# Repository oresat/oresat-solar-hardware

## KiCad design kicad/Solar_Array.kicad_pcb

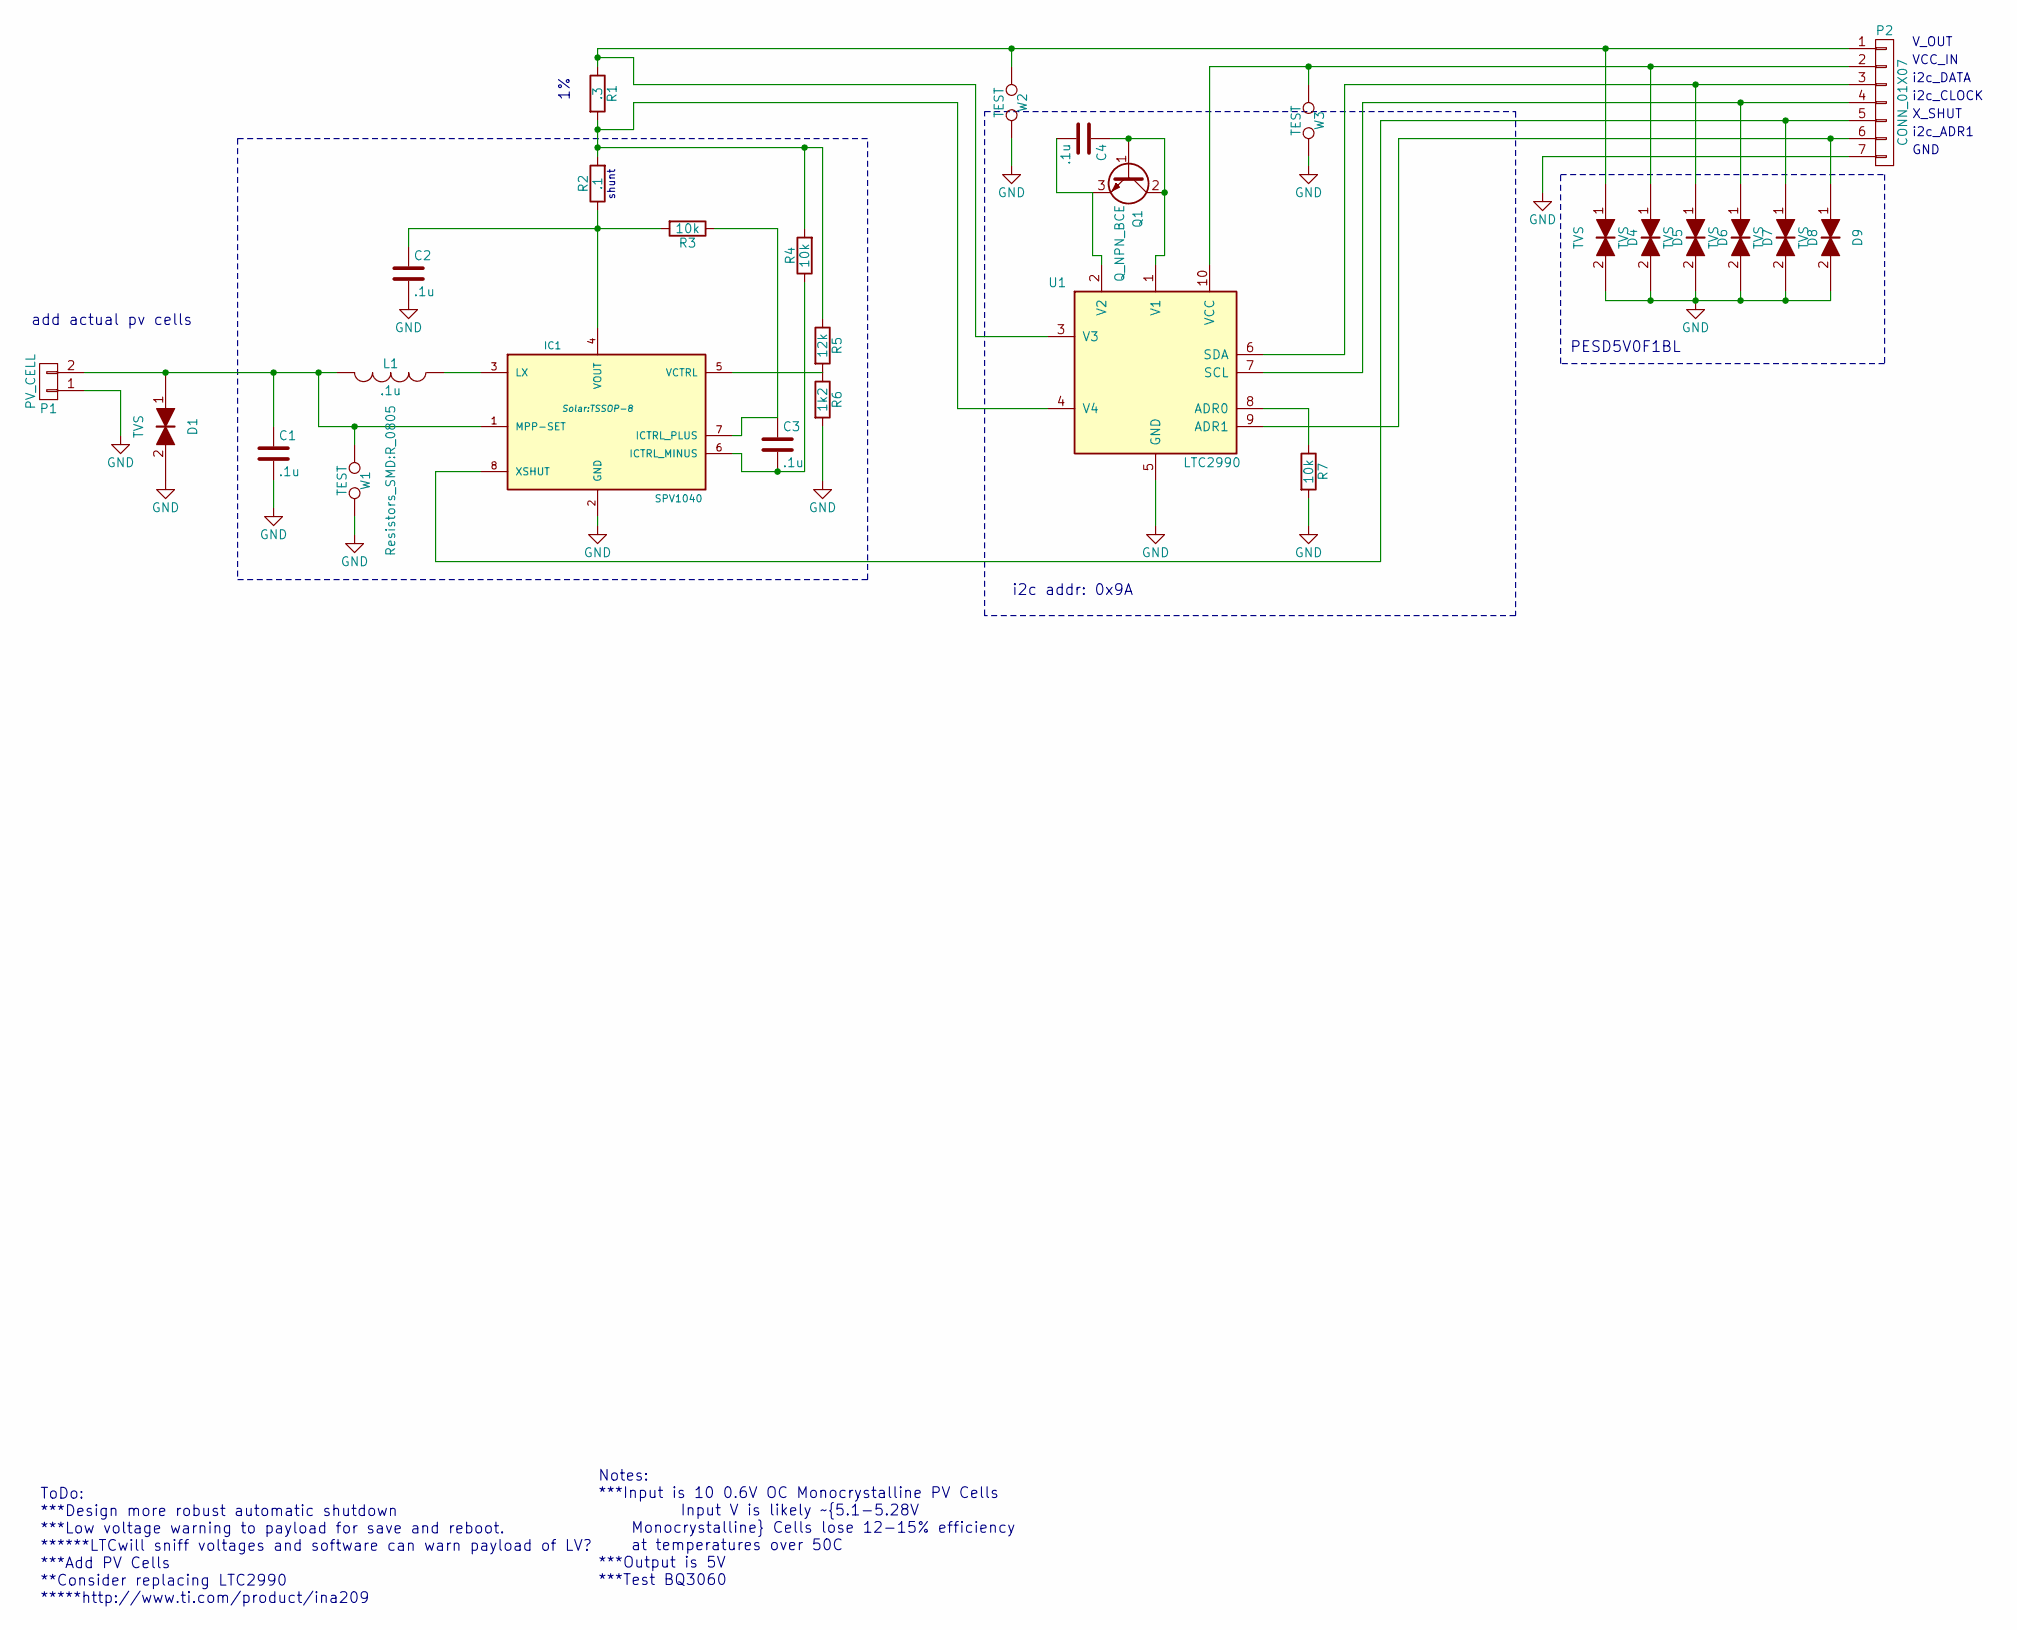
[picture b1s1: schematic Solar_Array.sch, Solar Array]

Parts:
C1, C2, C3, C4: .1u; C_0603
D1, D4, D5, D6, D7, D8, D9: TVS; SOD-882
IC1: SPV1040; TSSOP-8
L1: .1u; Inductor_1212
P1: PV_CELL; Pin_Header_Straight_1x02
P2: CONN_01X07; Pin_Header_Straight_1x07
Q1: Q_NPN_BCE; SOT-23
R1: .3; R_0402
R2: .1; R_0402
R3, R4, R7: 10k; R_0603
R5: 12k; R_0603
R6: 1k2; R_0603
U1: LTC2990; MSOP-10
W1, W2, W3: TEST; R_0805

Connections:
GND: C1.2, C2.2, D1.2, D4.2, D5.2, D6.2, D7.2, D8.2, D9.2, IC1.2 (GND), P1.1, P2.7, R6.2, R7.2, U1.5 (GND), W1.2, W2.2, W3.2
unnamed: C1.1, D1.1, IC1.1 (MPP-SET), L1.2, P1.2, W1.1
unnamed: C2.1, IC1.4 (VOUT), R2.1, R3.2
unnamed: C3.1, IC1.7 (ICTRL_PLUS), R3.1
unnamed: C3.2, IC1.6 (ICTRL_MINUS), R4.1
unnamed: C4.1, Q1.1 (B), Q1.2 (C), U1.1 (V1)
unnamed: C4.2, Q1.3 (E), U1.2 (V2)
unnamed: D4.1, P2.1, R1.1, U1.3 (V3), W2.1
unnamed: D5.1, P2.2, U1.10 (VCC), W3.1
unnamed: D6.1, P2.3, U1.6 (SDA)
unnamed: D7.1, P2.4, U1.7 (SCL)
unnamed: D8.1, IC1.8 (XSHUT), P2.5
unnamed: D9.1, P2.6, U1.9 (ADR1)
unnamed: IC1.3 (LX), L1.1
unnamed: IC1.5 (VCTRL), R5.2, R6.1
unnamed: R1.2, R2.2, R4.2, R5.1, U1.4 (V4)
unnamed: R7.1, U1.8 (ADR0)

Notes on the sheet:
i2c addr: 0x9A
ToDo: ***Design more robust automatic shutdown ***Low voltage warning to payload for save and reboot. ******LTCwill sniff voltages and software can warn payload of LV? ***Add PV Cells **Consider replacing LTC2990 *****http://www.ti.com/product/ina209
VCC_IN
Notes: ***Input is 10 0.6V OC Monocrystalline PV Cells Input V is likely ~5.1-5.28V Monocrystalline Cells lose 12-15% efficiency at temperatures over 50C ***Output is 5V ***Test BQ3060
V_OUT
i2c_DATA
i2c_CLOCK
X_SHUT
GND
i2c_ADR1
add actual pv cells
PESD5V0F1BL
shunt

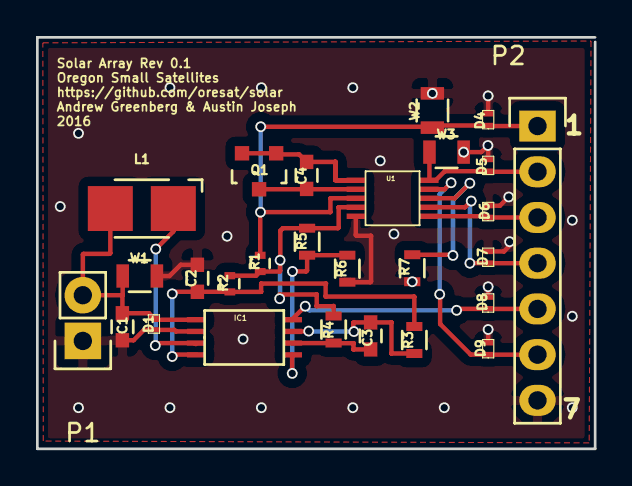
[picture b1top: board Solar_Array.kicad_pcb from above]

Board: 2 copper layers, 31.0 x 22.9 mm, 27 parts (0 on the bottom side), 17 nets.
